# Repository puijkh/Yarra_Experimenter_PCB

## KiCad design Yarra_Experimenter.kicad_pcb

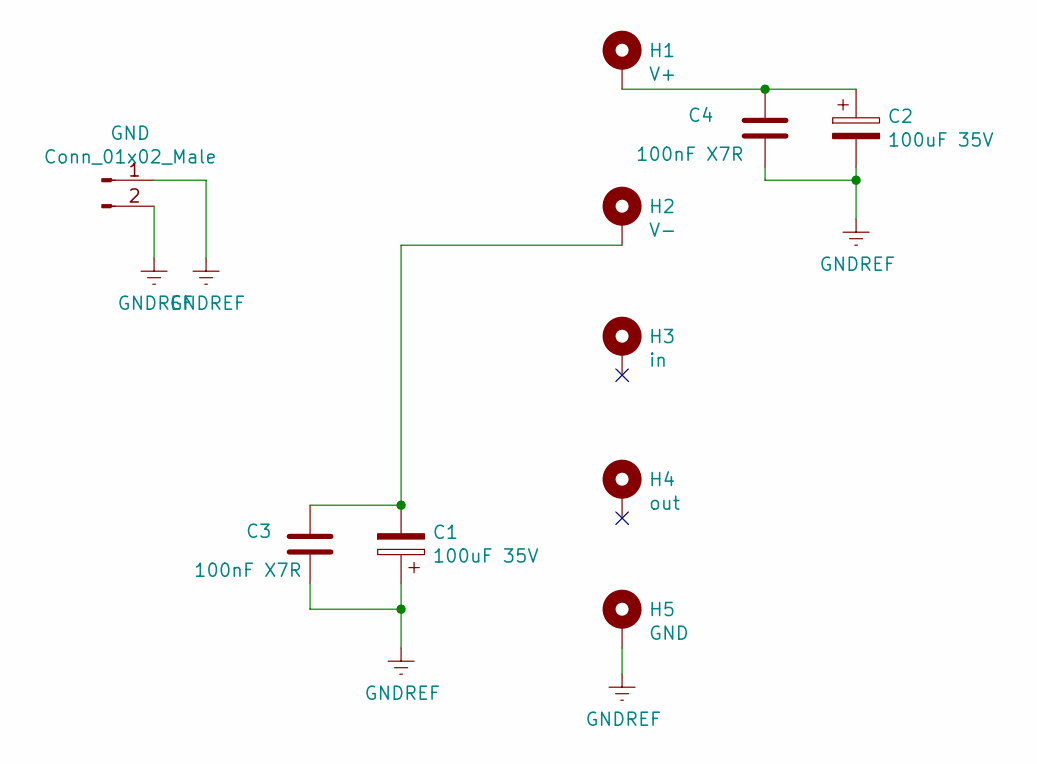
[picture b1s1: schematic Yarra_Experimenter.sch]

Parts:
C1, C2: 100uF 35V; CAPPRD500W85D1250H2700
C3, C4: 100nF X7R; C_Rect_L4.6mm_W4.6mm_P2.50mm_MKS02_FKP02
GND: Conn_01x02_Male; Molex_KK-254_AE-6410-02A_1x02_P2.54mm_Vertical
H1: V+; MountingHole_3.2mm_M3_Pad_TopBottom
H2: V-; MountingHole_3.2mm_M3_Pad_TopBottom
H3: in; MountingHole_3.2mm_M3_Pad_TopBottom
H4: out; MountingHole_3.2mm_M3_Pad_TopBottom
H5: GND; MountingHole_3.2mm_M3_Pad_TopBottom

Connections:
GNDREF: C1.1, C2.2, C3.2, C4.2, GND.1, GND.2, H5.1
unnamed: C1.2, C3.1, H2.1
unnamed: C2.1, C4.1, H1.1

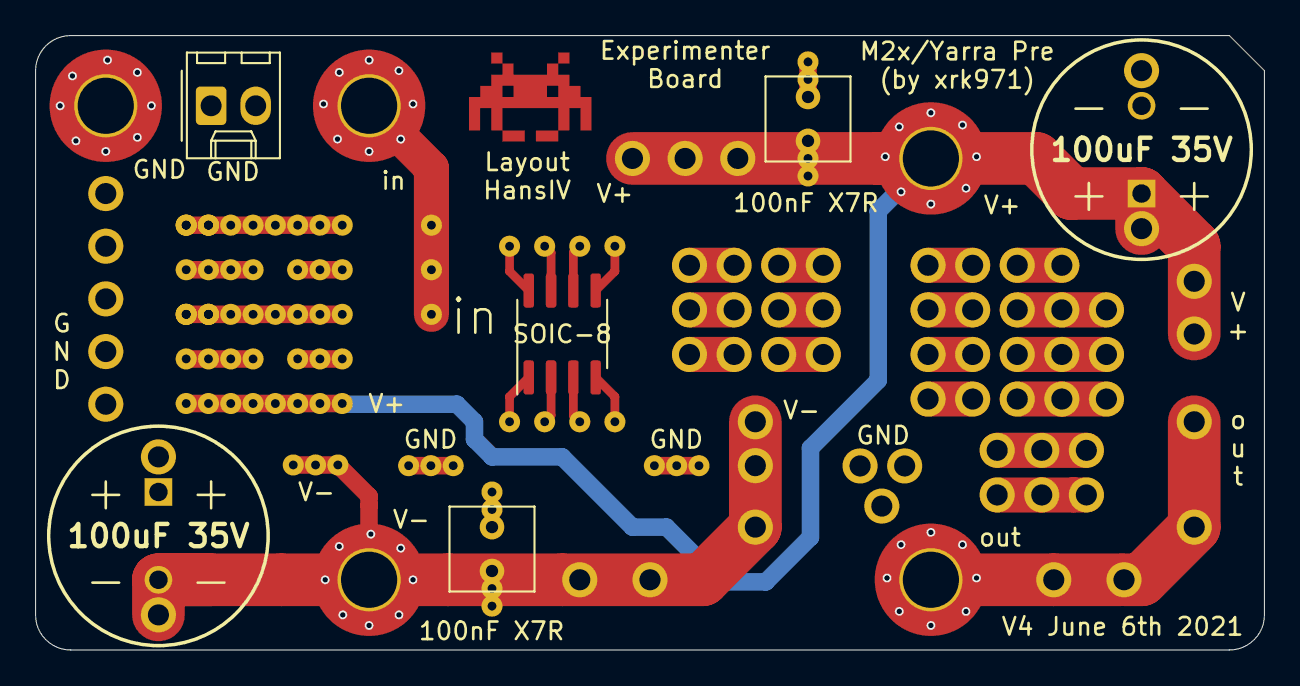
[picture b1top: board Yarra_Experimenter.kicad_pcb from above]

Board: 2 copper layers, 70.0 x 35.0 mm, 11 parts (0 on the bottom side), 3 nets.

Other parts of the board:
SOIC-8: SOIC-8; SOIC-8_3.9x4.9mm_P1.27mm

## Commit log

2021-06-06 V3 of the pre experimenter board
2021-06-06 Backside picture
2021-06-06 Saved the schematic
2021-06-06 Moved mounting /signal holes location to correct position
2021-06-06 Mechanical drawing
2021-06-06 With ground poor
2021-06-06 Removed 1 small left over via
2021-06-06 Saved
2021-06-07 Add image to the readme
2021-06-07 Add image with md instructions
